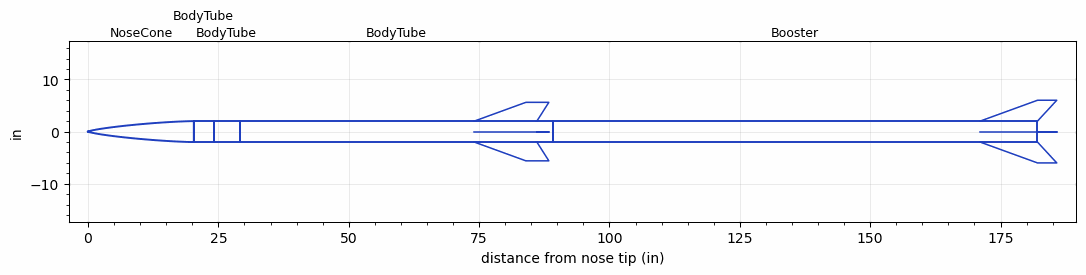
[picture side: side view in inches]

<RASAeroDocument>
 <FileVersion>2</FileVersion>
 <RocketDesign>
  <NoseCone>
   <Length>20.29</Length>
   <Diameter>4.02</Diameter>
   <Shape>Von Karman Ogive</Shape>
   <Location>0</Location>
  </NoseCone>
  <BodyTube>
   <Length>3.79</Length>
   <Diameter>4.02</Diameter>
   <Location>20.29</Location>
  </BodyTube>
  <BodyTube>
   <Length>5</Length>
   <Diameter>4.02</Diameter>
   <Location>24.08</Location>
  </BodyTube>
  <BodyTube>
   <Length>60</Length>
   <Diameter>4.02</Diameter>
   <Location>29.08</Location>
   <Fin>
    <Count>4</Count>
    <Chord>12</Chord>
    <Span>3.6</Span>
    <SweepDistance>9.891</SweepDistance>
    <TipChord>4.4</TipChord>
    <Thickness>0.28</Thickness>
    <LERadius>0.05</LERadius>
    <Location>15</Location>
    <AirfoilSection>Hexagonal</AirfoilSection>
    <FX1>0.6</FX1>
    <FX3>0.5</FX3>
   </Fin>
  </BodyTube>
  <Booster>
   <Length>93</Length>
   <Diameter>4.02</Diameter>
   <InsideDiameter>4.02</InsideDiameter>
   <Location>89.08</Location>
   <ShoulderLength>0</ShoulderLength>
   <Fin>
    <Count>4</Count>
    <Chord>11</Chord>
    <Span>4</Span>
    <SweepDistance>11</SweepDistance>
    <TipChord>3.7</TipChord>
    <Thickness>0.3</Thickness>
    <LERadius>0.05</LERadius>
    <Location>11</Location>
    <AirfoilSection>Hexagonal</AirfoilSection>
    <FX1>0.6</FX1>
    <FX3>0.4</FX3>
   </Fin>
  </Booster>
  <Surface>Camouflage Paint</Surface>
  <ModifiedBarrowman>True</ModifiedBarrowman>
  <Turbulence>True</Turbulence>
  <UseBooster1>False</UseBooster1>
  <UseBooster2>False</UseBooster2>
 </RocketDesign>
 <LaunchSite>
  <Altitude>1243</Altitude>
  <Pressure>0</Pressure>
  <RodAngle>3</RodAngle>
  <RodLength>12</RodLength>
  <Temperature>70</Temperature>
  <WindSpeed>10</WindSpeed>
 </LaunchSite>
 <Recovery>
  <Altitude1>1000</Altitude1>
  <Altitude2>1000</Altitude2>
  <DeviceType1>None</DeviceType1>
  <DeviceType2>None</DeviceType2>
  <Event1>False</Event1>
  <Event2>False</Event2>
  <Size1>1</Size1>
  <Size2>1</Size2>
  <EventType1>None</EventType1>
  <EventType2>None</EventType2>
  <CD1>1.33</CD1>
  <CD2>1.33</CD2>
 </Recovery>
 <SimulationList>
  <Simulation>
   <SustainerEngine>M1297W  (AT)</SustainerEngine>
   <SustainerLaunchWt>31.8</SustainerLaunchWt>
   <SustainerNozzleDiameter>2.25</SustainerNozzleDiameter>
   <SustainerCG>53.05</SustainerCG>
   <SustainerIgnitionDelay>8</SustainerIgnitionDelay>
   <Booster1Engine>N3300  (AT)</Booster1Engine>
   <Booster1LaunchWt>72.4</Booster1LaunchWt>
   <Booster1SeparationDelay>0</Booster1SeparationDelay>
   <Booster1IgnitionDelay>0</Booster1IgnitionDelay>
   <Booster1CG>109</Booster1CG>
   <Booster1NozzleDiameter>1.75</Booster1NozzleDiameter>
   <IncludeBooster1>True</IncludeBooster1>
   <Booster2Delay>0</Booster2Delay>
   <IncludeBooster2>False</IncludeBooster2>
   <TimetoApogee>50.41825</TimetoApogee>
   <MaxAltitude>38353.68</MaxAltitude>
   <MaxVelocity>1774.472</MaxVelocity>
  </Simulation>
 </SimulationList>
</RASAeroDocument>
